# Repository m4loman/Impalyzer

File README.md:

# Impalyzer
Impedance (spectrum) analyzer for microelectrodes based on AD5933

This is a simple impedance spectrum analyzer. The design (especially the oscillator and the analog frontend) is specifically tuned to the analysis of microelectrodes used in electrophysiology. Even though the AD5933 comes with its own signal generator on board, it needs to be clock divided to perform excitation frequencies of around 1000Hz properly.

I need to add a bypass circuit in the next revision for electroplating but hey.. this is a good start

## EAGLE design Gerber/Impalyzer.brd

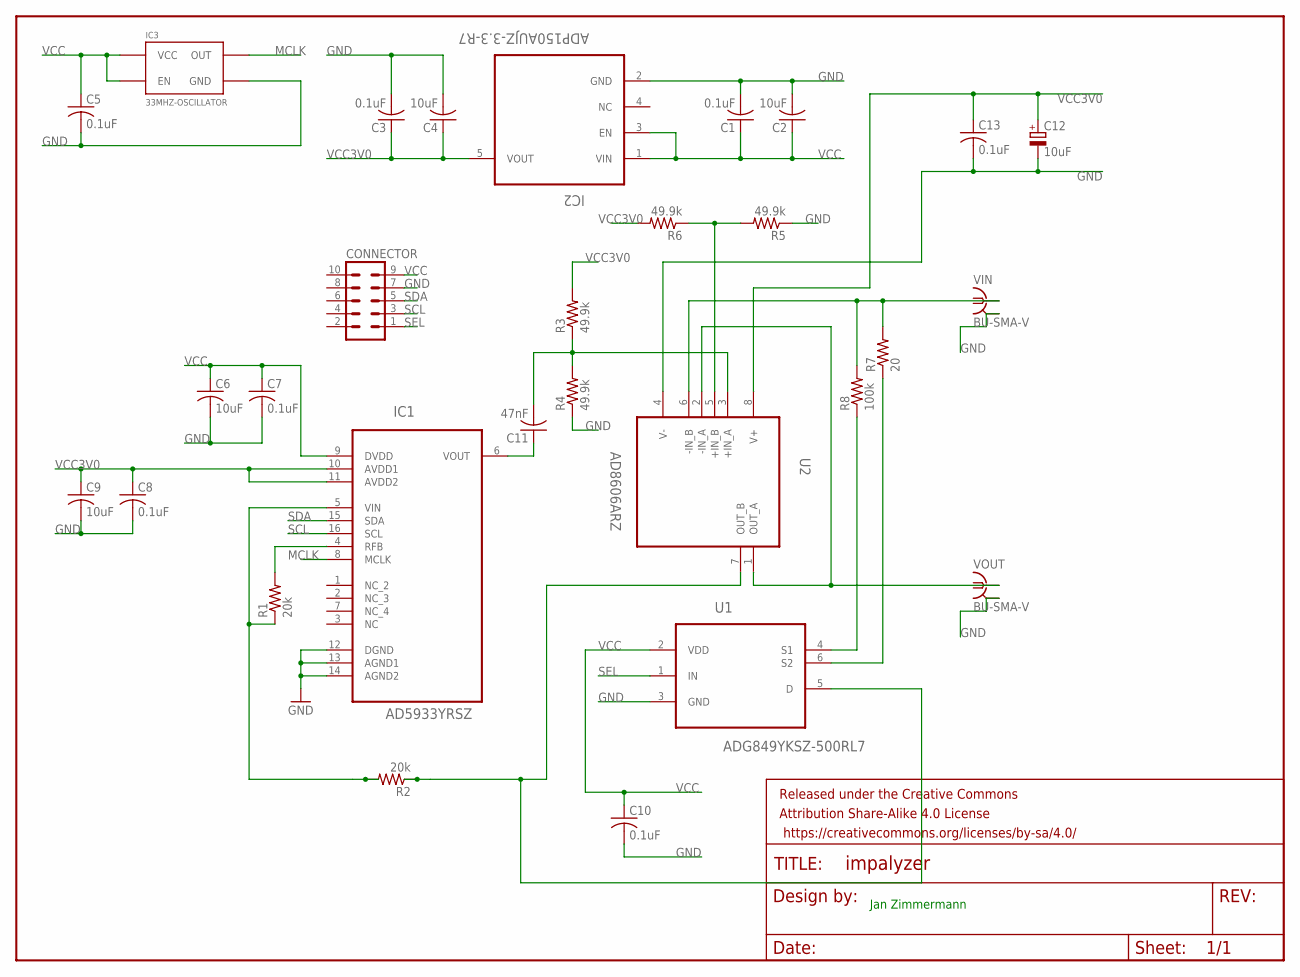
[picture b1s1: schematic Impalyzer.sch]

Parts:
C1, C3, C5, C7, C8, C10, C13: 0.1uF; C0402
C2, C4, C6, C9: 10uF; C0402
C11: 47nF; C0402
C12: 10uF; A/3216-18W
CONNECTOR: MA05-2
FRAME1: FRAME-LETTERNO_PACKAGE; DUMMY
IC1: AD5933YRSZ; SOP65P640X120-16N
IC2: ADP150AUJZ-3.3-R7; SOT95P280X100-5N
IC3: 33MHZ-OSCILLATOR; CRYSTAL-OSC-SMD-5X3.2
R1, R2: 20k; 0603-RES
R3, R4, R5, R6: 49.9k; 0603-RES
R7: 20; R2010
R8: 100k; 0603-RES
U1: ADG849YKSZ-500RL7; SOT65P210X110-6N
U2: AD8606ARZ; SOIC127P600X175-8N
VIN: BU-SMA-V
VOUT: BU-SMA-V

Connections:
GND: C1.2, C2.2, C3.2, C4.2, C5.2, C6.2, C7.2, C8.2, C9.2, C10.2, C12.-, C13.2, CONNECTOR.7, IC1.12 (DGND), IC1.13 (AGND1), IC1.14 (AGND2), IC2.2 (GND), IC3.2 (GND), R4.1, R5.1, U1.3 (GND), U2.4 (V-), VIN.2, VIN.3 (2), VIN.4 (2), VIN.5 (2), VOUT.2, VOUT.3 (2), VOUT.4 (2), VOUT.5 (2)
MCLK: IC1.8 (MCLK), IC3.3 (OUT)
unnamed: R2.1, U1.5 (D), U2.7 (OUT_B)
unnamed: C11.1, IC1.6 (VOUT)
unnamed: IC1.4 (RFB), R1.2
unnamed: IC1.5 (VIN), R1.1, R2.2
unnamed: U2.1 (OUT_A), U2.2 (-IN_A), VOUT.1
unnamed: R7.2, R8.2, U2.6 (-IN_B), VIN.1
unnamed: C11.2, R3.1, R4.2, U2.3 (+IN_A)
unnamed: R5.2, R6.1, U2.5 (+IN_B)
unnamed: R8.1, U1.4 (S1)
unnamed: R7.1, U1.6 (S2)
SCL: CONNECTOR.3, IC1.16 (SCL)
SDA: CONNECTOR.5, IC1.15 (SDA)
SEL: CONNECTOR.1, U1.1 (IN)
VCC: C1.1, C2.1, C5.1, C6.1, C7.1, C10.1, CONNECTOR.9, IC1.9 (DVDD), IC2.1 (VIN), IC2.3 (EN), IC3.1 (EN), IC3.4 (VCC), U1.2 (VDD)
VCC3V0: C3.1, C4.1, C8.1, C9.1, C12.+, C13.1, IC1.10 (AVDD1), IC1.11 (AVDD2), IC2.5 (VOUT), R3.2, R6.2, U2.8 (V+)

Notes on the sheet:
Jan Zimmermann

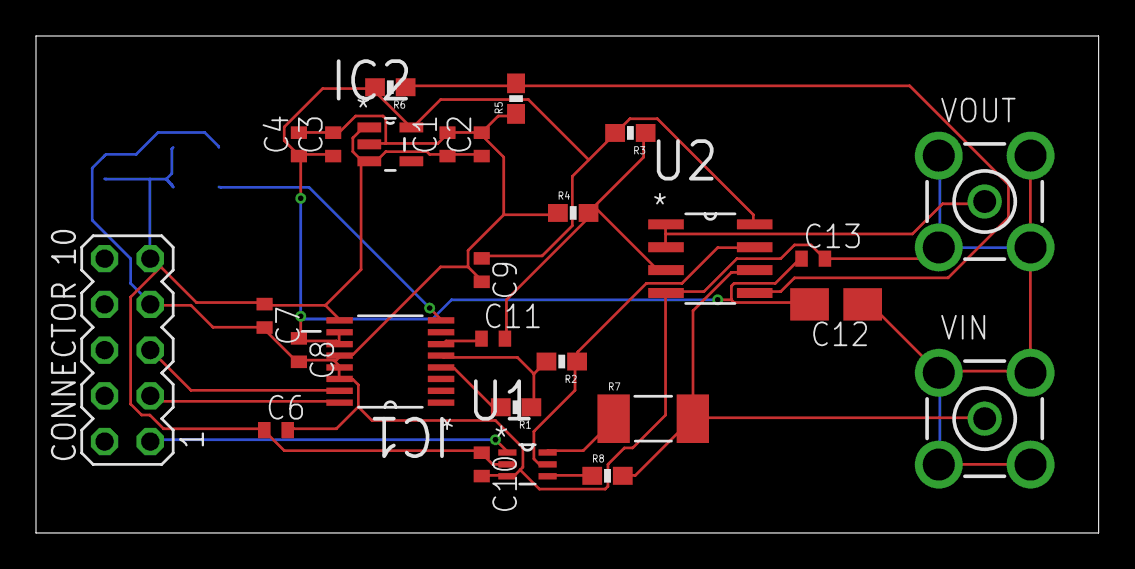
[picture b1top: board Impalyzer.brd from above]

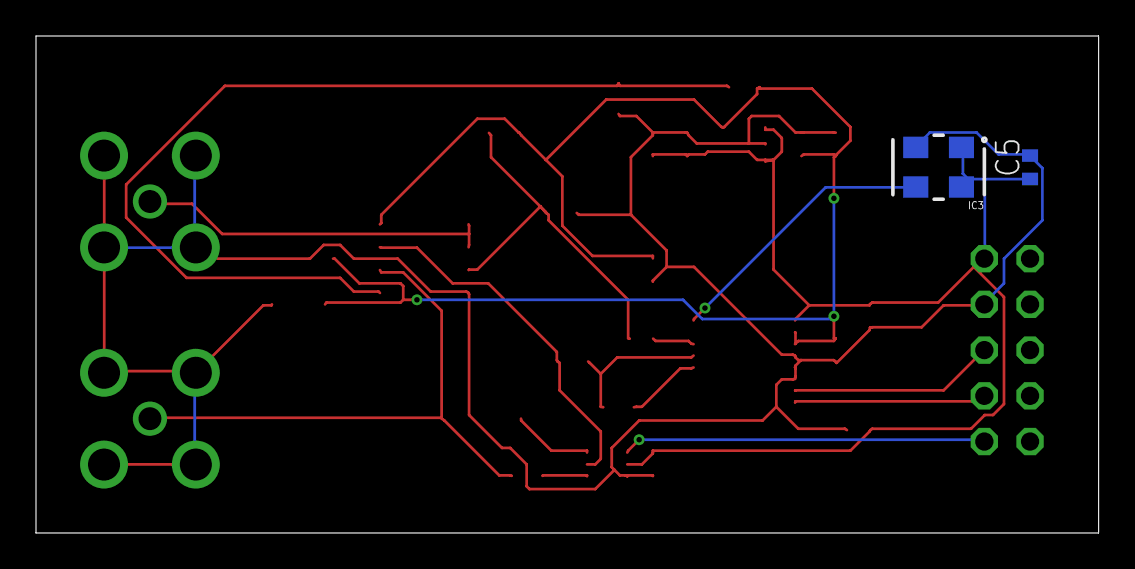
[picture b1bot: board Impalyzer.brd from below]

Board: 2 copper layers, 59.0 x 27.6 mm, 30 parts (2 on the bottom side), 17 nets.

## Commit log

2016-07-26 init

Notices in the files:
parts and their libraries:
SparkFun-Aesthetics: Licensing: Creative Commons ShareAlike 4.0 International - https://creativecommons.org/licenses/by-sa/4.0
SparkFun-Aesthetics: Released under the Creative Commons Attribution Share-Alike 4.0 License
SparkFun-Aesthetics: https://creativecommons.org/licenses/by-sa/4.0
